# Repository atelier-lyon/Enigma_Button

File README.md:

# Enigma Button

## By Florian "FloRide" Reimat

## About

This repo is the Button panel PCB of the Enigma project

## Images:

### Schematic:

### PCB:

|                Front                |               Bottom               |
| :---------------------------------: | :--------------------------------: |
|  |  |

### 3D:

|                  Front                  |                Bottom                |
| :-------------------------------------: | :----------------------------------: |
|    |  |
|                Tilted 1                 |               Tilted 2               |
|  |   |

## Others:

- [Interactive BOM](Export/ibom/Enigma_Button-ibom.html)
- [BOM](Export/bom/Enigma_Button-bom.csv)
- [Cost](Export/cost/Enigma_Button-kicost.xlsx)

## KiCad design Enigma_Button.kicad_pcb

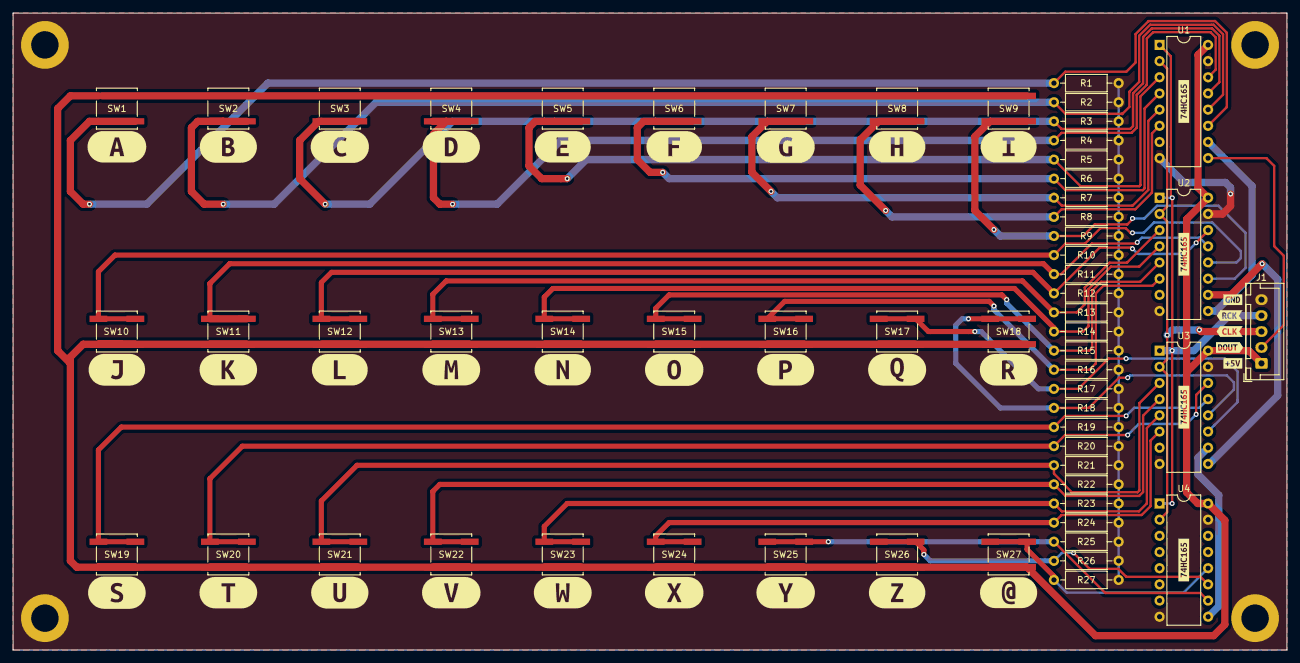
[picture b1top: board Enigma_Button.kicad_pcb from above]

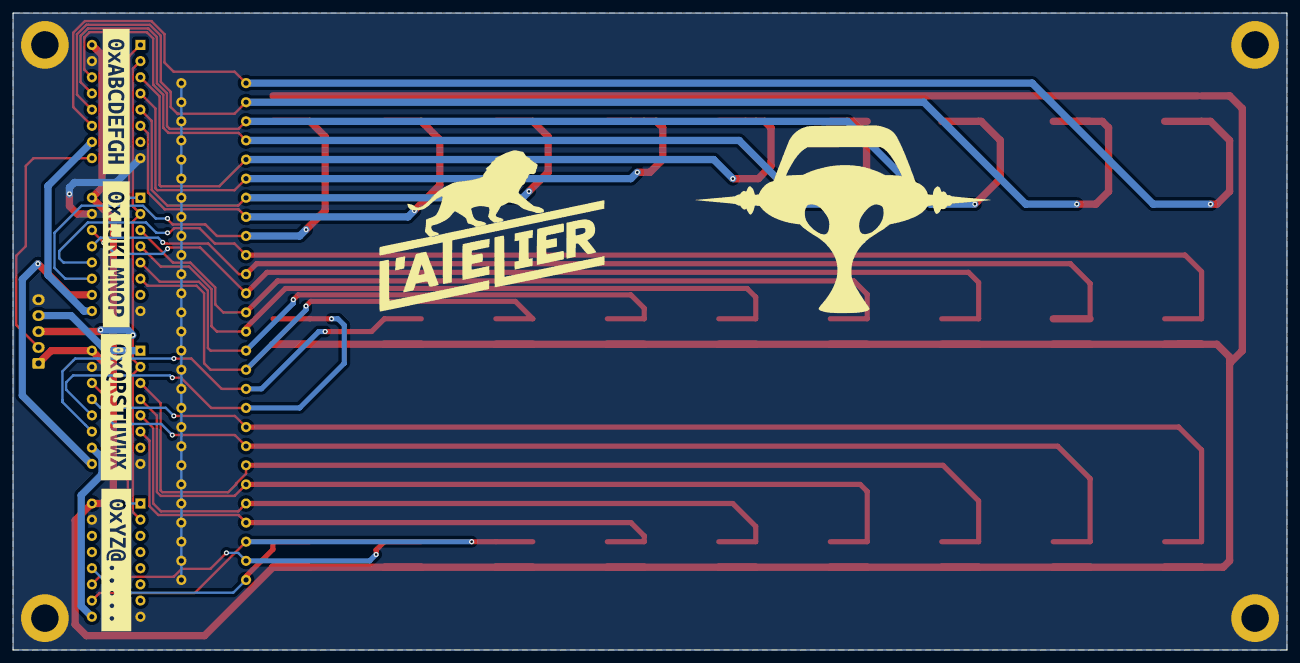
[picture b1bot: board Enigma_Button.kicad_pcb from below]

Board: 2 copper layers, 200.0 x 100.0 mm, 103 parts (4 on the bottom side), 35 nets.

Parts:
H1, H2, H3, H4: MountingHole_Pad; MountingHole_4.3mm_M4_DIN965_Pad
J1: Conn_01x05; JST_XH_B5B-XH-A_1x05_P2.50mm_Vertical
R1, R2, R3, R4, R5, R6, R7, R8, R9, R10, R11, R12, R13, R14, R15, R16, R17, R18, R19, R20, R21, R22, R23, R24, R25, R26, R27: 10k; R_Axial_DIN0207_L6.3mm_D2.5mm_P10.16mm_Horizontal
SW1, SW2, SW3, SW4, SW5, SW6, SW7, SW8, SW9, SW10, SW11, SW12, SW13, SW14, SW15, SW16, SW17, SW18, SW19, SW20, SW21, SW22, SW23, SW24, SW25, SW26, SW27: SW_Push_Dual_x2; SW_Push_1P1T_NO_CK_KSC6xxJ
U1, U2, U3, U4: 74HC165; DIP-16_W7.62mm
kibuzzard-63711D6C: G***; kibuzzard-63711D6C
kibuzzard-63711D37: G***; kibuzzard-63711D37
kibuzzard-63711D53: G***; kibuzzard-63711D53
kibuzzard-63711D65: G***; kibuzzard-63711D65
kibuzzard-63711ECF: G***; kibuzzard-63711ECF
kibuzzard-63711ED5: G***; kibuzzard-63711ED5
kibuzzard-63711EDA: G***; kibuzzard-63711EDA
kibuzzard-63711EDF: G***; kibuzzard-63711EDF
kibuzzard-63711EFB: G***; kibuzzard-63711EFB
kibuzzard-63711EFF: G***; kibuzzard-63711EFF
kibuzzard-63711F3D: G***; kibuzzard-63711F3D
kibuzzard-63711F4B: G***; kibuzzard-63711F4B
kibuzzard-63711F44: G***; kibuzzard-63711F44
kibuzzard-63711F50: G***; kibuzzard-63711F50
kibuzzard-63711F55: G***; kibuzzard-63711F55
kibuzzard-63711F59: G***; kibuzzard-63711F59
kibuzzard-63711F68: G***; kibuzzard-63711F68
kibuzzard-63711FE1: G***; kibuzzard-63711FE1
kibuzzard-63711FE6: G***; kibuzzard-63711FE6
kibuzzard-63711FEC: G***; kibuzzard-63711FEC
kibuzzard-63715E68, kibuzzard-63715E68#2, kibuzzard-63715E68#3, kibuzzard-63715E68#4: G***; kibuzzard-63715E68
kibuzzard-63715F3F: G***; kibuzzard-63715F3F
kibuzzard-63715F4E: G***; kibuzzard-63715F4E
kibuzzard-63715F23: G***; kibuzzard-63715F23
kibuzzard-63715F28: G***; kibuzzard-63715F28
kibuzzard-63715FDB: G***; kibuzzard-63715FDB
kibuzzard-6371201D: G***; kibuzzard-6371201D
kibuzzard-6371615D: G***; kibuzzard-6371615D
kibuzzard-63712013: G***; kibuzzard-63712013
kibuzzard-63712018: G***; kibuzzard-63712018
kibuzzard-63712021: G***; kibuzzard-63712021
kibuzzard-63712027: G***; kibuzzard-63712027
kibuzzard-63714482: G***; kibuzzard-63714482
kibuzzard-63714697: G***; kibuzzard-63714697
kibuzzard-63716105: G***; kibuzzard-63716105
kibuzzard-63716137: G***; kibuzzard-63716137
kibuzzard-63716148: G***; kibuzzard-63716148

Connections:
+5V: J1.1, SW1.1 (C), SW2.1 (C), SW3.1 (C), SW4.1 (C), SW5.1 (C), SW6.1 (C), SW7.1 (C), SW8.1 (C), SW9.1 (C), SW10.1 (C), SW11.1 (C), SW12.1 (C), SW13.1 (C), SW14.1 (C), SW15.1 (C), SW16.1 (C), SW17.1 (C), SW18.1 (C), SW19.1 (C), SW20.1 (C), SW21.1 (C), SW22.1 (C), SW23.1 (C), SW24.1 (C), SW25.1 (C), SW26.1 (C), SW27.1 (C), U1.16 (VCC), U2.16 (VCC), U3.16 (VCC), U4.16 (VCC)
/INPUT_@: R27.1, SW27.2 (D), U4.12 (D1)
/INPUT_A: R1.1, SW1.2 (D), U1.11 (D0)
/INPUT_B: R2.1, SW2.2 (D), U1.12 (D1)
/INPUT_C: R3.1, SW3.2 (D), U1.13 (D2)
/INPUT_D: R4.1, SW4.2 (D), U1.14 (D3)
/INPUT_E: R5.1, SW5.2 (D), U1.3 (D4)
/INPUT_F: R6.1, SW6.2 (D), U1.4 (D5)
/INPUT_G: R7.1, SW7.2 (D), U1.5 (D6)
/INPUT_H: R8.1, SW8.2 (D), U1.6 (D7)
/INPUT_I: R9.1, SW9.2 (D), U2.11 (D0)
/INPUT_J: R10.1, SW10.2 (D), U2.12 (D1)
/INPUT_K: R11.1, SW11.2 (D), U2.13 (D2)
/INPUT_L: R12.1, SW12.2 (D), U2.14 (D3)
/INPUT_M: R13.1, SW13.2 (D), U2.3 (D4)
/INPUT_N: R14.1, SW14.2 (D), U2.4 (D5)
/INPUT_O: R15.1, SW15.2 (D), U2.5 (D6)
/INPUT_P: R16.1, SW16.2 (D), U2.6 (D7)
/INPUT_Q: R17.1, SW17.2 (D), U3.11 (D0)
/INPUT_R: R18.1, SW18.2 (D), U3.12 (D1)
/INPUT_S: R19.1, SW19.2 (D), U3.13 (D2)
/INPUT_T: R20.1, SW20.2 (D), U3.14 (D3)
/INPUT_U: R21.1, SW21.2 (D), U3.3 (D4)
/INPUT_V: R22.1, SW22.2 (D), U3.4 (D5)
/INPUT_W: R23.1, SW23.2 (D), U3.5 (D6)
/INPUT_X: R24.1, SW24.2 (D), U3.6 (D7)
/INPUT_Y: R25.1, SW25.2 (D), U4.10 (DS)
/INPUT_Z: R26.1, SW26.2 (D), U4.11 (D0)
GND: H1.1, H2.1, H3.1, H4.1, J1.5, R1.2, R2.2, R3.2, R4.2, R5.2, R6.2, R7.2, R8.2, R9.2, R10.2, R11.2, R12.2, R13.2, R14.2, R15.2, R16.2, R17.2, R18.2, R19.2, R20.2, R21.2, R22.2, R23.2, R24.2, R25.2, R26.2, R27.2, U1.8 (GND), U1.15 (~CE), U2.8 (GND), U2.15 (~CE), U3.8 (GND), U3.15 (~CE), U4.8 (GND), U4.15 (~CE)
INPUT_CLK: J1.3, U1.2 (CP), U2.2 (CP), U3.2 (CP), U4.2 (CP)
INPUT_DOUT: J1.2, U1.9 (Q7)
INPUT_RCK: J1.4, U1.1 (~PL), U2.1 (~PL), U3.1 (~PL), U4.1 (~PL)
unnamed: U1.10 (DS), U2.9 (Q7)
unnamed: U2.10 (DS), U3.9 (Q7)
unnamed: U3.10 (DS), U4.9 (Q7)

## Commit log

2022-11-15 [ROOT] Initial commit
2022-11-15 [PRO][SCH][PCB] Add Kicad files
2022-11-15 [CI/CD] Add CI/CD + Kibot
